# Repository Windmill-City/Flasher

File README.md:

<h1 align="center">Flasher</h1>

<p align="center">
  基于 WCH CH582F 的 USB ISP 烧录器与 USB ↔ UART 透传工具
</p>

<p align="center">

</p>

> A compact CH582F-based USB ISP flasher and USB ↔ UART bridge for WCH CH570/CH572 dongles.

## 简介

Flasher 是一块 USB 棒形态的小板：USB-C 接电脑，USB-A 接目标板。它可以在两种角色间切换：

- **烧录器**：作为 USB Host 接管目标板，进入 WCH 的 USB ISP Bootloader，完成识别、解锁、擦除、写入与校验。
- **透传桥**：把电脑的 CDC 串口桥接到目标板的 USB CDC/Bulk 端点，或者把 USB-A 上的 D-/D+ 复用为 3.3 V TTL UART。

固件为裸机 C++17，直接操作 CH582F 寄存器，不依赖 WCH SDK；上位机脚本 `firmware/tools/flasher.py` 提供命令行操作。

## 功能特性

- **USB-C 供电与通信**：CH582F 原生 USB2.0 全速设备，枚举为 CDC ACM（`1A86:5721`）。
- **目标 USB-A 口**：支持 USB Host 枚举，板载 MT9700 负载开关可通过 `PB4` 独立控制目标 VBUS，实现硬复位/重新上电。
- **WCH ISP 烧录**：识别 `4348:55E0` / `1A86:55E0` Bootloader，支持 CH570/CH572 的解锁流程（清理 code flash 标记 / `CFG_DEBUG_EN`）、整片擦除、分块写入与回读校验，最大 240 KiB。
- **Master 透传**：PC CDC ↔ 目标 CDC/Bulk，同步 `SET_LINE_CODING` 与 `SET_CONTROL_LINE_STATE`（DTR/RTS）。
- **Slave 透传**：PC CDC ↔ USB-A 引脚上的 UART1（PB13 TX / PB12 RX），波特率跟随 PC 端串口设置。
- **状态指示**：USB 枚举成功后 LED 常亮，否则 500 ms 闪烁；BOOT 按键可让 CH582F 自身进入下载模式。
- **生产就绪**：提供 Gerber、BOM、坐标文件与 IPC 网表。

## 硬件

| 项目 | 参数 |
| --- | --- |
| MCU | WCH CH582F（RISC-V，448 KB Flash / 32 KB RAM，双 USB2.0 全速） |
| 主时钟 | 32 MHz 无源晶振，PLL 480 MHz / 6 = 80 MHz |
| 电脑侧接口 | USB-C（HRO TYPE-C-31-M-12），CC 5.1 kΩ 下拉 |
| 目标侧接口 | USB-A（XKB U231-091N-4BLRA00-S） |
| 3.3 V 电源 | HR6206A33T3 LDO |
| 目标 VBUS 开关 | MT9700 负载开关，`PB4` 使能 |
| 指示/按键 | LED（`PA12`，高有效）、BOOT 按键（`PB22`） |
| PCB | 43 × 16 mm，2 层，0.8 mm 厚，圆角 |

上图为 KiCad 10 通过 `kicad-cli pcb render` 生成的真实 3D 渲染（非布局截图）。元件全部布置在正面，背面可查看走线与铺铜。

<details>
<summary>查看背面 3D 渲染</summary>

</details>

## 仓库结构

```
.
├── Flasher.kicad_pro / .kicad_sch / .kicad_pcb   # KiCad 工程（原理图 + PCB）
├── Custom.kicad_sym                              # 自定义符号库
├── production/                                   # Gerber、BOM、坐标、IPC 网表
├── docs/images/                                  # KiCad 3D 渲染图
└── firmware/
    ├── Makefile                                  # RISC-V GCC 构建
    ├── ld/ch582.ld                               # 链接脚本
    ├── include/ch582/                            # 寄存器、USB、ISP、UART 等头文件
    ├── src/                                      # 裸机固件与中断启动代码
    └── tools/flasher.py                          # PC 端命令行工具
```

## 固件构建

### 依赖

- GNU Make
- MounRiver Studio 3 自带的 WCH RISC-V Embedded GCC 工具链
  （默认路径 `C:/MounRiver/MounRiver_Studio3/resources/app/resources/win32/components/WCH/Toolchain/RISC-V Embedded GCC15/bin`）

### 编译

```bash
cd firmware
make
```

若工具链不在默认位置：

```bash
make MRS_TOOLCHAIN="/path/to/RISC-V Embedded GCC/bin"
```

输出位于 `firmware/build/`：

| 文件 | 说明 |
| --- | --- |
| `flasher.hex` | Intel HEX，烧录到 CH582F |
| `flasher.bin` | 原始二进制 |
| `flasher.elf` / `.map` | 调试符号与内存映射 |

### 给 Flasher 本身烧录固件

1. 按住 **BOOT** 键（拉低 `PB22`）。
2. 通过 USB-C 接入电脑，CH582F 进入内置 USB ISP 模式。
3. 使用 WCHISPTool 选择 `firmware/build/flasher.hex` 下载到 `0x00000000`。
4. 重新上电，设备枚举为 CDC 串口 `1A86:5721`。

## 使用

### 安装上位机依赖

```bash
pip install pyserial
```

`flasher.py` 可自动按 VID/PID 查找串口，也可以显式指定 `--port COMx`。

### 常用命令

```bash
# 查看协议版本、当前模式、目标类型与 VID/PID
python flasher.py --port COM7 info

# Master 透传：桥接 USB-A 上的目标设备，并打开终端监视
python flasher.py --port COM7 master --monitor

# Slave 透传：USB-A 作为 115200 8N1 的 3.3V UART
python flasher.py --port COM7 slave --baud 115200 --monitor

# 通过 WCH ISP 烧录镜像，写入后回读校验
python flasher.py --port COM7 flash firmware.bin --verify

# 目标电源控制：off / app / isp
python flasher.py --port COM7 power isp

# 发送 BREAK，从透传模式返回命令模式
python flasher.py --port COM7 reset
```

> 透传模式下串口为原始字节流；发送 **BREAK** 可随时打断桥接并回到命令模式。Windows 下 USB BREAK 可能滞后于后续数据，脚本会自动重试 PING 确认。

## 串口协议

命令模式固定使用 115200 8N1，帧格式如下（多字节字段均为小端）：

```
请求:  AA 55 | CMD | LEN | PAYLOAD[LEN] | CRC8
应答:  55 AA | CMD | LEN | PAYLOAD[LEN] | CRC8
```

- `CRC8`：多项式 `0x07`，初值 `0x00`，覆盖 `CMD | LEN | PAYLOAD`。
- `LEN` 最大 64；ISP 数据块为 4 字节地址 + 56 字节数据。

| CMD | 名称 | 请求载荷 | 说明 |
| --- | --- | --- | --- |
| `0x01` | PING | — | 返回状态、协议版本、模式、目标类型、VID/PID |
| `0x02` | INFO | — | 同 PING |
| `0x03` | SET_MODE | `mode [, baud:u32]` | `0` 空闲 / `1` Master / `2` Slave |
| `0x04` | POWER | `on, boot` | `0` 断电；`1,0` 上电到应用；`1,1` 上电到 Bootloader |
| `0x10` | ISP_BEGIN | `size:u32` | 进入 ISP、解锁并擦除，返回芯片信息与 UID |
| `0x11` | ISP_WRITE | `addr:u32 + data` | 写入最多 56 字节 |
| `0x12` | ISP_VERIFY | `addr:u32 + data` | 回读校验 |
| `0x13` | ISP_FINISH | — | 结束会话并把目标复位到应用 |

| 状态码 | 含义 |
| --- | --- |
| `0x00` | OK |
| `0x01` | 未知命令 |
| `0x02` | 参数错误 |
| `0x03` | 未检测到目标 |
| `0x04` | USB 错误 |
| `0x05` | ISP 错误 |
| `0x07` | 不支持 |

## 实现要点

- **USB Host 电源时序**：Slave 模式下先在数据线悬空时给目标上电，让目标 Bootloader 采样到 D+ 为低并启动应用，随后再初始化 UART；否则 D+ 被驱动为高会把目标困在 ISP 模式。
- **ISP 解锁**：部分 CH570/CH572 需要先清除代码区标记或 `CFG_DEBUG_EN`，解锁后重新枚举再执行擦写。
- **零长度包**：USB 传输对 64 字节整数倍长度会补 ZLP，保证端点事务正常结束。
- **锁定与中断安全**：CDC 行编码/控制线状态通过 generation 计数同步，关键区使用 `CriticalSection` 关中断保护。
- **无 SDK 依赖**：`include/ch582/platform/registers.hpp` 自行定义外设寄存器与中断号，便于裁剪和审计。

## 3D 渲染与生产文件

3D 图片由 KiCad 10 命令行直接渲染：

```bash
kicad-cli pcb render --width 1600 --height 900 --quality high \
  --side top --background transparent --floor --perspective --zoom 1.05 \
  -o docs/images/board-top.png Flasher.kicad_pcb

kicad-cli pcb render --width 1600 --height 1000 --quality high \
  --side top --background transparent --floor --perspective \
  --rotate "-35,0,25" -o docs/images/board-iso.png Flasher.kicad_pcb

kicad-cli pcb render --width 1600 --height 900 --quality high \
  --side bottom --background transparent --floor --perspective --zoom 1.05 \
  -o docs/images/board-bottom.png Flasher.kicad_pcb
```

`production/Flasher-1.0.zip` 包含可直接送厂的 Gerber；BOM、元件坐标与 IPC 网表位于同一目录。

## 许可证

本项目采用 [Apache License 2.0](LICENSE) 开源。

Copyright 2026 Windmill_City

---

相关链接：[WCH CH582 产品页](https://www.wch.cn/products/CH582.html) · [项目仓库](https://github.com/Windmill-City/Flasher)

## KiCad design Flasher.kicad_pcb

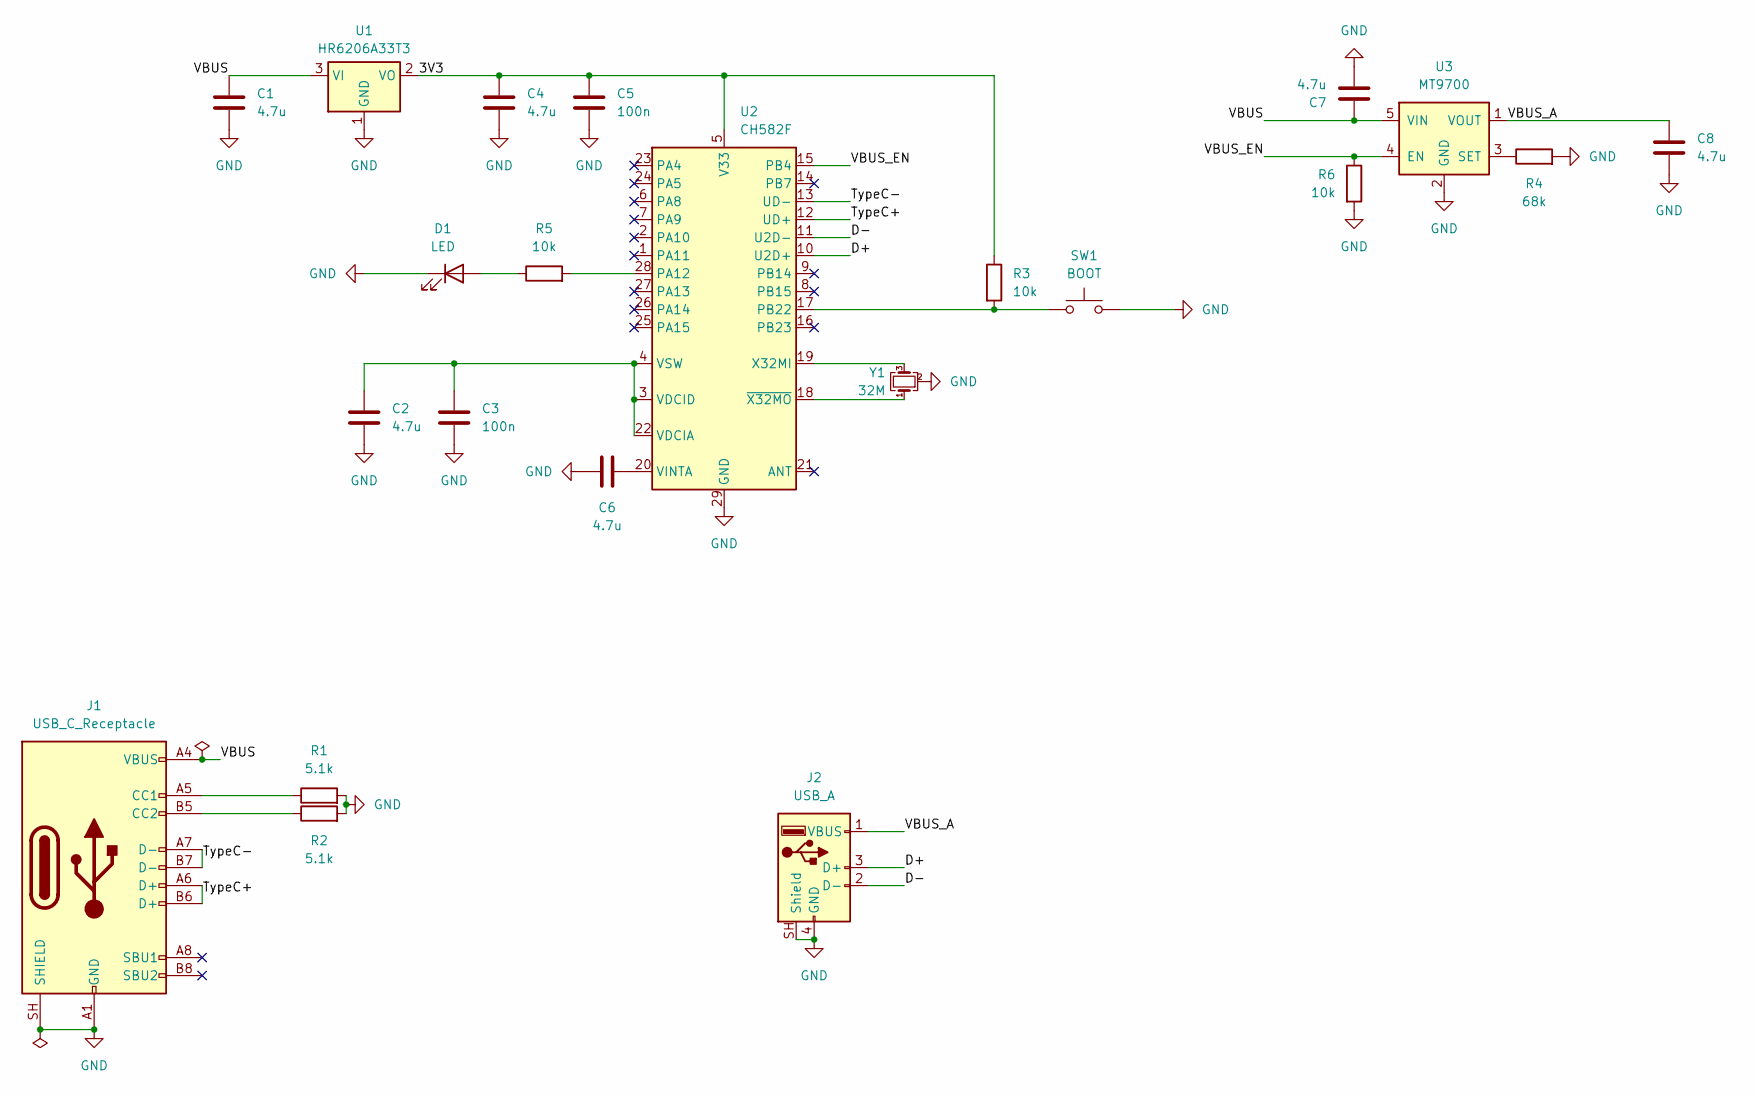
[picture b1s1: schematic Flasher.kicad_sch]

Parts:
C1, C2, C4, C6, C7, C8: 4.7u; C_0402_1005Metric
C3, C5: 100n; C_0402_1005Metric
D1: LED; LED_0402_1005Metric
J1: USB_C_Receptacle; USB_C_Receptacle_HRO_TYPE-C-31-M-12
J2: USB_A; USB_A_Receptacle_XKB_U231-091N-4BLRA00-S
R1, R2: 5.1k; R_0402_1005Metric
R3, R5, R6: 10k; R_0402_1005Metric
R4: 68k; R_0402_1005Metric
SW1: BOOT; SW_Push_SPST_NO_Alps_SKRK
U1: HR6206A33T3; SOT-23
U2: CH582F; WQFN-28-1EP_4x4mm_P0.4mm_EP2.7x2.7mm
U3: MT9700; SOT-23-5
Y1: 32M; Crystal_SMD_2016-4Pin_2.0x1.6mm

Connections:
/3V3: C4.1, C5.1, R3.1, U1.2 (VO), U2.5 (V33)
/D+: J2.3 (D+), U2.10 (U2D+)
/D-: J2.2 (D-), U2.11 (U2D-)
/TypeC+: J1.A6 (D+), J1.B6 (D+), U2.12 (UD+)
/TypeC-: J1.A7 (D-), J1.B7 (D-), U2.13 (UD-)
/VBUS: C1.1, C7.1, J1.A4 (VBUS), J1.A9 (VBUS), J1.B4 (VBUS), J1.B9 (VBUS), U1.3 (VI), U3.5 (VIN)
/VBUS_A: C8.1, J2.1 (VBUS), U3.1 (VOUT)
/VBUS_EN: R6.1, U2.15 (PB4), U3.4 (EN)
GND: C1.2, C2.2, C3.2, C4.2, C5.2, C6.2, C7.2, C8.2, D1.1 (K), J1.A1 (GND), J1.A12 (GND), J1.B1 (GND), J1.B12 (GND), J1.SH (SHIELD), J2.4 (GND), J2.SH (Shield), R1.2, R2.2, R4.2, R6.2, SW1.2, U1.1 (GND), U2.29 (GND), U3.2 (GND), Y1.2 (G), Y1.4 (G)
unnamed: D1.2 (A), R5.1
unnamed: J1.A5 (CC1), R1.1
unnamed: J1.B5 (CC2), R2.1
unnamed: R5.2, U2.28 (PA12)
unnamed: R3.2, SW1.1, U2.17 (PB22)
unnamed: C2.1, C3.1, U2.3 (VDCID), U2.4 (VSW), U2.22 (VDCIA)
unnamed: C6.1, U2.20 (VINTA)
unnamed: U2.19 (X32MI), Y1.3
unnamed: U2.18 (~X32MO), Y1.1
unnamed: R4.1, U3.3 (SET)

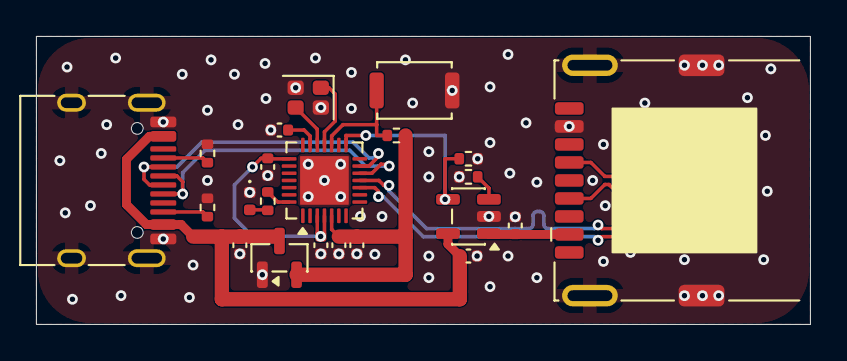
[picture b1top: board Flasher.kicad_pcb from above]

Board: 2 copper layers, 43.0 x 16.0 mm, 22 parts (0 on the bottom side), 19 nets.

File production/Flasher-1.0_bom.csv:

Designator,Footprint,Quantity,Value,LCSC Part #
"C1, C2, C4, C6, C7, C8",0402,6,4.7u,
"C3, C5",0402,2,100n,
D1,0402,1,LED,
J1,USB_C_Receptacle_HRO_TYPE-C-31-M-12,1,USB_C_Receptacle,
J2,USB_A_Receptacle_XKB_U231-091N-4BLRA00-S,1,USB_A,
"R1, R2",0402,2,5.1k,
"R3, R5, R6",0402,3,10k,
R4,0402,1,68k,
SW1,SW_Push_SPST_NO_Alps_SKRK,1,BOOT,
U1,SOT-23,1,HR6206A33T3,
U2,WQFN-28-1EP_4x4mm_P0.4mm_EP2.7x2.7mm,1,CH582F,
U3,SOT-23-5,1,MT9700,
Y1,Crystal_SMD_2016-4Pin_2.0x1.6mm,1,32M,

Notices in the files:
README.md:
License: Apache 2.0
